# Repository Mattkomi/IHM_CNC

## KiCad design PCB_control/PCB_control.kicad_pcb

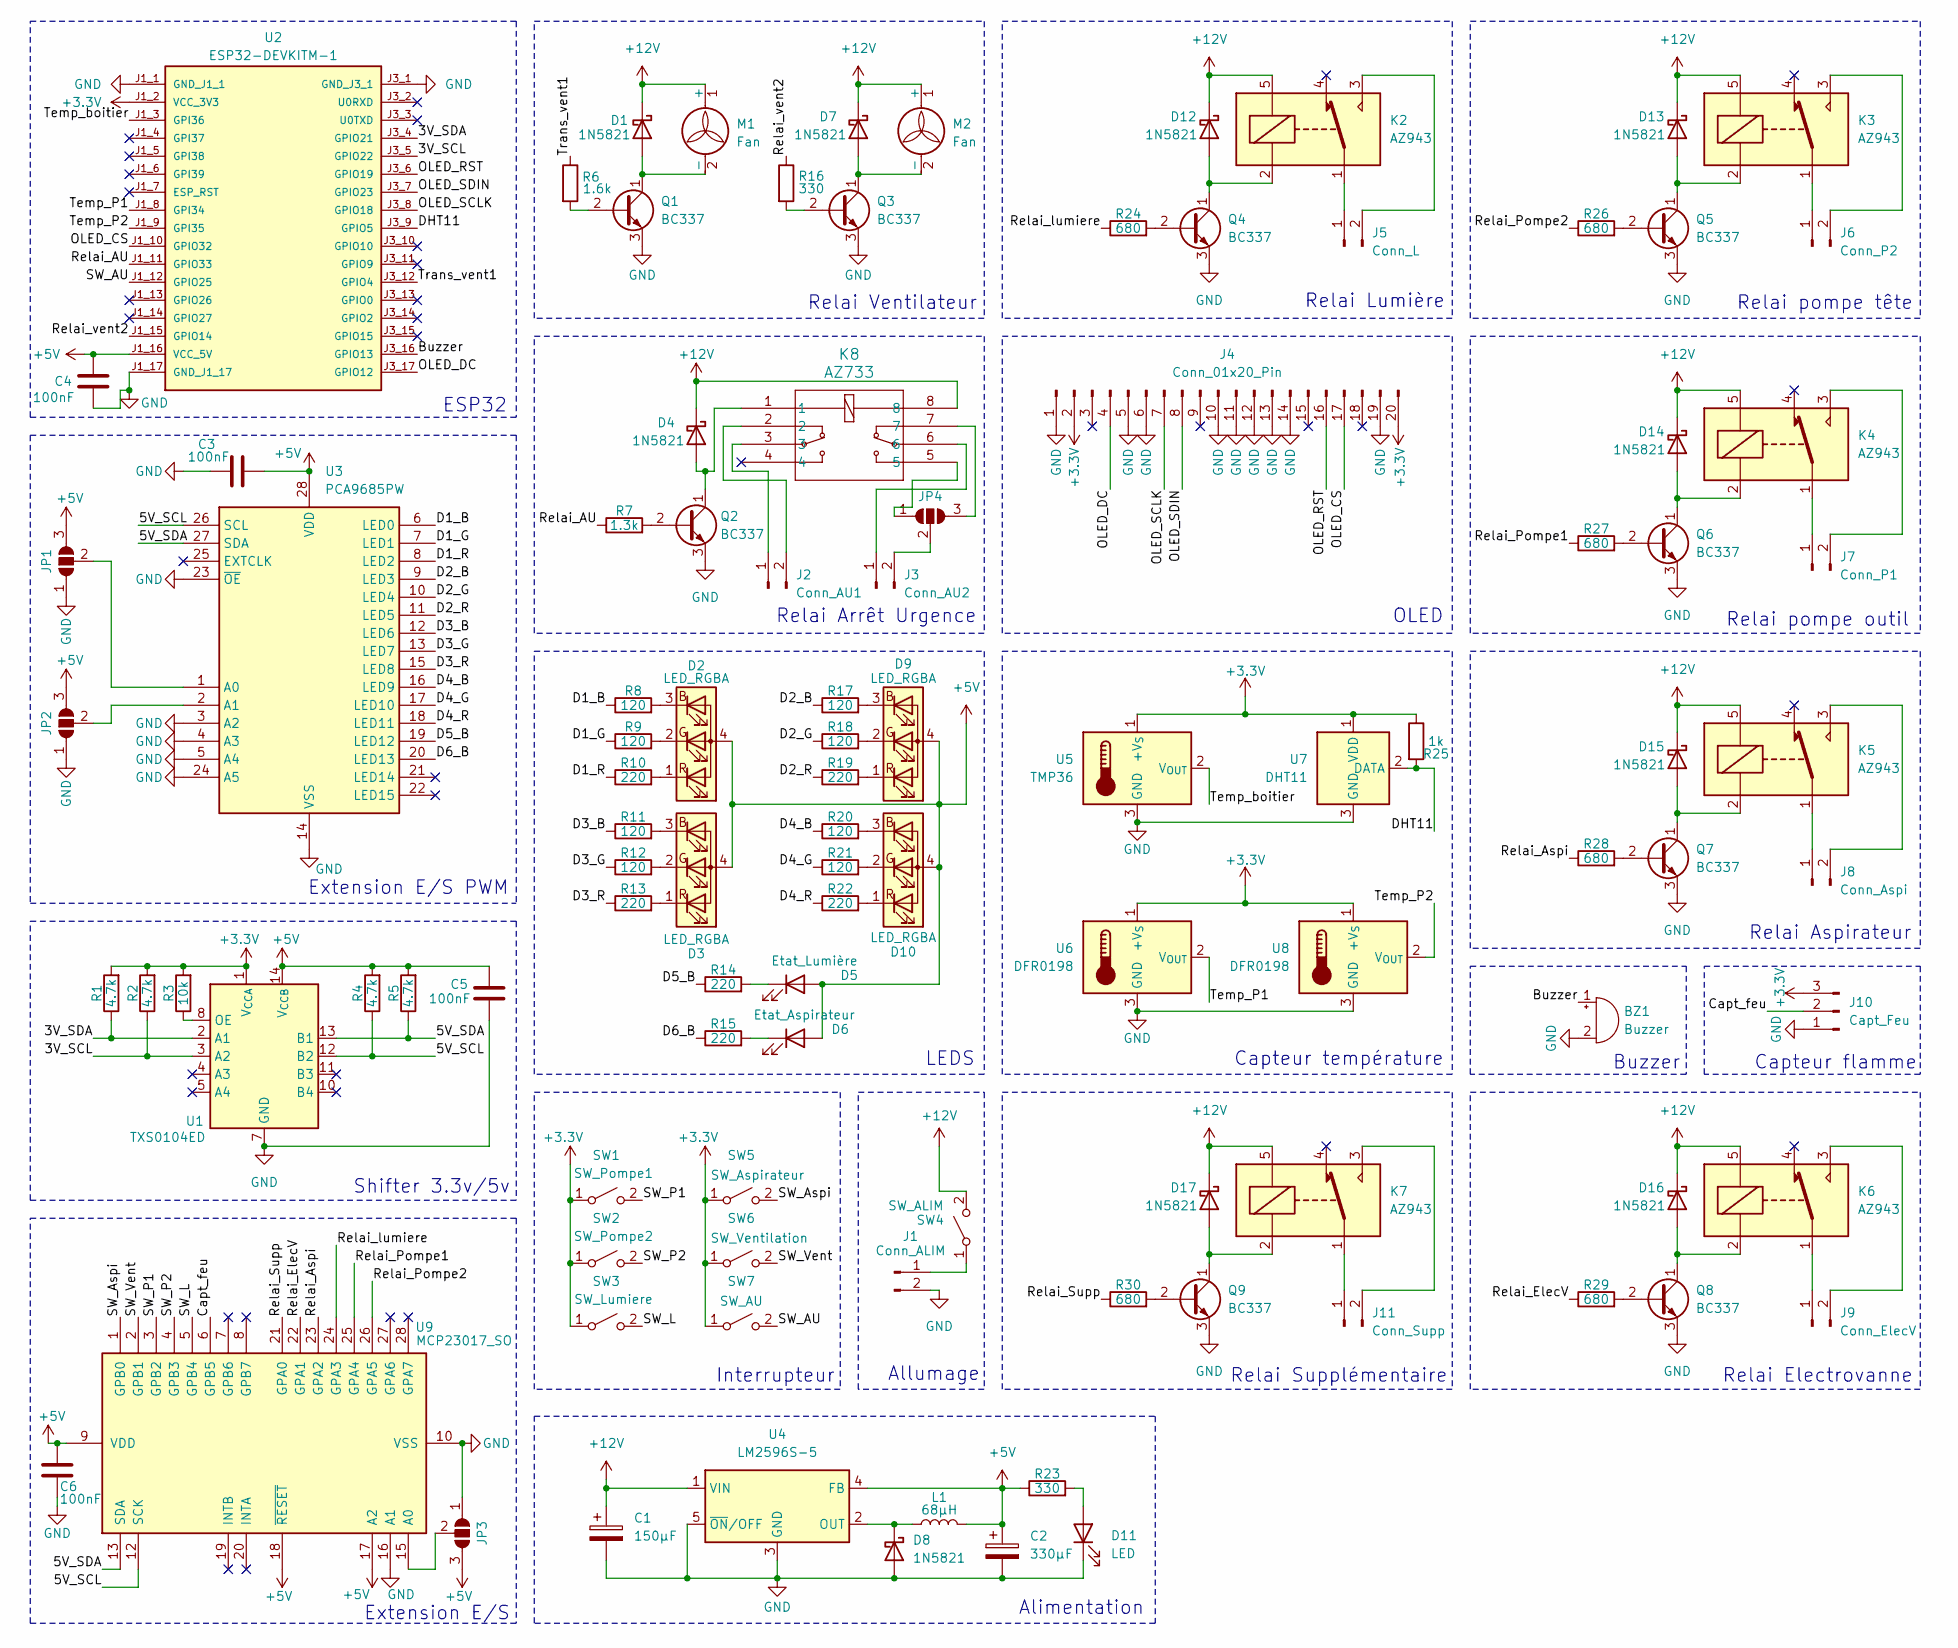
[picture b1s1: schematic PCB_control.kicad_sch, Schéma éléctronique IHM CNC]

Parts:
BZ1: Buzzer; WST-1205S
C1: 150µF; CP_Radial_D6.3mm_P2.50mm
C2: 330µF; CP_Radial_D8.0mm_P3.50mm
C3, C4, C5, C6: 100nF; CAP_R82D-7P4X2P6-5P0_KEM
D1, D4, D7, D8, D12, D13, D14, D15, D16, D17: 1N5821; P2_DO-201
D2, D3, D9, D10: LED_RGBA; JST_XH_B4B-XH-A_1x04_P2.50mm_Vertical
D5: Etat_Lumière; JST_XH_B2B-XH-A_1x02_P2.50mm_Vertical
D6: Etat_Aspirateur; JST_XH_B2B-XH-A_1x02_P2.50mm_Vertical
D11: LED; JST_XH_B2B-XH-A_1x02_P2.50mm_Vertical
J1: Conn_ALIM; JST_XH_B2B-XH-A_1x02_P2.50mm_Vertical
J2: Conn_AU1; Molex_Micro-Fit_3.0_43045-0200_2x01_P3.00mm_Horizontal
J3: Conn_AU2; Molex_Micro-Fit_3.0_43045-0200_2x01_P3.00mm_Horizontal
J4: Conn_01x20_Pin; JST_XH_B20B-XH-A_1x20_P2.50mm_Vertical
J5: Conn_L; Molex_Micro-Fit_3.0_43045-0200_2x01_P3.00mm_Horizontal
J6: Conn_P2; Molex_Micro-Fit_3.0_43045-0200_2x01_P3.00mm_Horizontal
J7: Conn_P1; Molex_Micro-Fit_3.0_43045-0200_2x01_P3.00mm_Horizontal
J8: Conn_Aspi; Molex_Micro-Fit_3.0_43045-0200_2x01_P3.00mm_Horizontal
J9: Conn_ElecV; Molex_Micro-Fit_3.0_43045-0200_2x01_P3.00mm_Horizontal
J10: Capt_Feu; JST_XH_S3B-XH-A_1x03_P2.50mm_Horizontal
J11: Conn_Supp; Molex_Micro-Fit_3.0_43045-0200_2x01_P3.00mm_Horizontal
JP1, JP2, JP3: SolderJumper_3_Open; SolderJumper-3_P1.3mm_Open_RoundedPad1.0x1.5mm
JP4: SolderJumper_3_Open; SolderJumper-3_P1.3mm_Open_RoundedPad1.0x1.5mm_NumberLabels
K2, K3, K4, K5, K6, K7: AZ943; AZ943-1CH_AMZ
K8: AZ733; AZ733-2C_AMZ
L1: 68µH; L_Bourns_SRR1260
M1: Fan; JST_XH_B2B-XH-A_1x02_P2.50mm_Vertical
M2: Fan; JST_XH_S2B-XH-A-1_1x02_P2.50mm_Horizontal
Q1, Q2, Q3, Q4, Q5, Q6, Q7, Q8, Q9: BC337; TO-92_Inline
R1, R2, R4, R5: 4.7k; R_1206_3216Metric_Pad1.30x1.75mm_HandSolder
R3: 10k; R_1206_3216Metric_Pad1.30x1.75mm_HandSolder
R6: 1.6k; R_1206_3216Metric_Pad1.30x1.75mm_HandSolder
R7: 1.3k; R_1206_3216Metric_Pad1.30x1.75mm_HandSolder
R8, R9, R11, R12, R17, R18, R20, R21: 120; R_1206_3216Metric_Pad1.30x1.75mm_HandSolder
R10, R13, R14, R15, R19, R22: 220; R_1206_3216Metric_Pad1.30x1.75mm_HandSolder
R16, R23: 330; R_1206_3216Metric_Pad1.30x1.75mm_HandSolder
R24, R26, R27, R28, R29, R30: 680; R_1206_3216Metric_Pad1.30x1.75mm_HandSolder
R25: 1k; R_1206_3216Metric_Pad1.30x1.75mm_HandSolder
SW1: SW_Pompe1; JST_XH_B2B-XH-A_1x02_P2.50mm_Vertical
SW2: SW_Pompe2; JST_XH_B2B-XH-A_1x02_P2.50mm_Vertical
SW3: SW_Lumiere; JST_XH_B2B-XH-A_1x02_P2.50mm_Vertical
SW4: SW_ALIM; JST_XH_B2B-XH-A_1x02_P2.50mm_Vertical
SW5: SW_Aspirateur; JST_XH_B2B-XH-A_1x02_P2.50mm_Vertical
SW6: SW_Ventilation; JST_XH_B2B-XH-A_1x02_P2.50mm_Vertical
SW7: SW_AU; JST_XH_B2B-XH-A_1x02_P2.50mm_Vertical
U1: TXS0104ED; SOIC-14_3.9x8.7mm_P1.27mm
U2: ESP32-DEVKITM-1; MODULE_ESP32-DEVKITM-1; PARTREV 1.0
U3: PCA9685PW; TSSOP-28_4.4x9.7mm_P0.65mm
U4: LM2596S-5; TO-263-5_TabPin3
U5: TMP36; TO-92_Inline
U6, U8: DFR0198; JST_XH_S3B-XH-A_1x03_P2.50mm_Horizontal
U7: DHT11; JST_XH_S3B-XH-A_1x03_P2.50mm_Horizontal
U9: MCP23017_SO; TSSOP-28_4.4x9.7mm_P0.65mm

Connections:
+3.3V: J4.2, J4.20, J10.3, R1.2, R2.2, R3.2, R25.1, SW1.1 (A), SW2.1 (A), SW3.1 (A), SW5.1 (A), SW6.1 (A), SW7.1 (A), U1.1 (V_{CCA}), U2.J1_2 (VCC_3V3), U5.1 (+V_{S}), U6.1 (+V_{S}), U7.1 (VDD), U8.1 (+V_{S})
+5V: C2.1, C3.2, C4.1, C5.1, C6.1, D2.4 (A), D3.4 (A), D5.2 (A), D6.2 (A), D9.4 (A), D10.4 (A), JP1.3 (B), JP2.3 (B), JP3.3 (B), L1.2, R4.2, R5.2, R23.1, U1.14 (V_{CCB}), U2.J1_16 (VCC_5V), U3.28 (VDD), U4.4 (FB), U9.9 (VDD), U9.17 (A2), U9.18 (~RESET)
+12V: C1.1, D1.1 (K), D4.1 (K), D7.1 (K), D12.1 (K), D13.1 (K), D14.1 (K), D15.1 (K), D16.1 (K), D17.1 (K), K2.5, K3.5, K4.5, K5.5, K6.5, K7.5, K8.8, M1.1 (+), M2.1 (+), SW4.2 (B), U4.1 (VIN)
/3V_SCL: R2.1, U1.3 (A2), U2.J3_5 (GPIO22)
/3V_SDA: R1.1, U1.2 (A1), U2.J3_4 (GPIO21)
/5V_SCL: R4.1, U1.12 (B2), U3.26 (SCL), U9.12 (SCK)
/5V_SDA: R5.1, U1.13 (B1), U3.27 (SDA), U9.13 (SDA)
/Buzzer: BZ1.1 (+), U2.J3_16 (GPIO13)
/Capt_feu: J10.2, U9.6 (GPB5)
/D1_B: R8.1, U3.6 (LED0)
/D1_G: R9.1, U3.7 (LED1)
/D1_R: R10.1, U3.8 (LED2)
/D2_B: R17.1, U3.9 (LED3)
/D2_G: R18.1, U3.10 (LED4)
/D2_R: R19.1, U3.11 (LED5)
/D3_B: R11.1, U3.12 (LED6)
/D3_G: R12.1, U3.13 (LED7)
/D3_R: R13.1, U3.15 (LED8)
/D4_B: R20.1, U3.16 (LED9)
/D4_G: R21.1, U3.17 (LED10)
/D4_R: R22.1, U3.18 (LED11)
/D5_B: R14.1, U3.19 (LED12)
/D6_B: R15.1, U3.20 (LED13)
/DHT11: R25.2, U2.J3_9 (GPIO5), U7.2 (DATA)
/OLED_CS: J4.17, U2.J1_10 (GPIO32)
/OLED_DC: J4.4, U2.J3_17 (GPIO12)
/OLED_RST: J4.16, U2.J3_6 (GPIO19)
/OLED_SCLK: J4.7, U2.J3_8 (GPIO18)
/OLED_SDIN: J4.8, U2.J3_7 (GPIO23)
/Relai_AU: R7.1, U2.J1_11 (GPIO33)
/Relai_Aspi: R28.1, U9.23 (GPA2)
/Relai_ElecV: R29.1, U9.22 (GPA1)
/Relai_Pompe1: R27.1, U9.25 (GPA4)
/Relai_Pompe2: R26.1, U9.26 (GPA5)
/Relai_Supp: R30.1, U9.21 (GPA0)
/Relai_lumiere: R24.1, U9.24 (GPA3)
/Relai_vent2: R16.1, U2.J1_15 (GPIO14)
/SW_AU: SW7.2 (B), U2.J1_12 (GPIO25)
/SW_Aspi: SW5.2 (B), U9.1 (GPB0)
/SW_L: SW3.2 (B), U9.5 (GPB4)
/SW_P1: SW1.2 (B), U9.3 (GPB2)
/SW_P2: SW2.2 (B), U9.4 (GPB3)
/SW_Vent: SW6.2 (B), U9.2 (GPB1)
/Temp_P1: U2.J1_8 (GPI34), U6.2 (V_{OUT})
/Temp_P2: U2.J1_9 (GPI35), U8.2 (V_{OUT})
/Temp_boitier: U2.J1_3 (GPI36), U5.2 (V_{OUT})
/Trans_vent1: R6.1, U2.J3_12 (GPIO4)
GND: BZ1.2 (-), C1.2, C2.2, C3.1, C4.2, C5.2, C6.2, D8.2 (A), D11.1 (K), J1.2, J4.1, J4.5, J4.6, J4.10, J4.11, J4.12, J4.13, J4.14, J4.19, J10.1, JP1.1 (A), JP2.1 (A), JP3.1 (A), Q1.3 (E), Q2.3 (E), Q3.3 (E), Q4.3 (E), Q5.3 (E), Q6.3 (E), Q7.3 (E), Q8.3 (E), Q9.3 (E), U1.7 (GND), U2.J1_1 (GND_J1_1), U2.J1_17 (GND_J1_17), U2.J3_1 (GND_J3_1), U3.3 (A2), U3.4 (A3), U3.5 (A4), U3.14 (VSS), U3.23 (~OE), U3.24 (A5), U4.3 (GND), U4.5 (~ON/OFF), U5.3 (GND), U6.3 (GND), U7.3 (GND), U8.3 (GND), U9.10 (VSS), U9.16 (A1)
unnamed: D1.2 (A), M1.2 (-), Q1.1 (C)
unnamed: D2.3 (BK), R8.2
unnamed: D2.2 (GK), R9.2
unnamed: D2.1 (RK), R10.2
unnamed: D3.3 (BK), R11.2
unnamed: D3.2 (GK), R12.2
unnamed: D3.1 (RK), R13.2
unnamed: D4.2 (A), K8.1, Q2.1 (C)
unnamed: D5.1 (K), R14.2
unnamed: D6.1 (K), R15.2
unnamed: D7.2 (A), M2.2 (-), Q3.1 (C)
unnamed: D8.1 (K), L1.1, U4.2 (OUT)
unnamed: D9.3 (BK), R17.2
unnamed: D9.2 (GK), R18.2
unnamed: D9.1 (RK), R19.2
unnamed: D10.3 (BK), R20.2
unnamed: D10.2 (GK), R21.2
unnamed: D10.1 (RK), R22.2
unnamed: D11.2 (A), R23.2
unnamed: D12.2 (A), K2.2, Q4.1 (C)
unnamed: D13.2 (A), K3.2, Q5.1 (C)
unnamed: D14.2 (A), K4.2, Q6.1 (C)
unnamed: D15.2 (A), K5.2, Q7.1 (C)
unnamed: D16.2 (A), K6.2, Q8.1 (C)
unnamed: D17.2 (A), K7.2, Q9.1 (C)
unnamed: J1.1, SW4.1 (A)
unnamed: J2.1, K8.3
unnamed: J2.2, K8.2
unnamed: J3.1, K8.6
unnamed: J3.2, JP4.2 (C)
unnamed: J5.1, K2.1
unnamed: J5.2, K2.3
unnamed: J6.1, K3.1
unnamed: J6.2, K3.3
unnamed: J7.1, K4.1
unnamed: J7.2, K4.3
unnamed: J8.1, K5.1
unnamed: J8.2, K5.3
unnamed: J9.1, K6.1
unnamed: J9.2, K6.3
unnamed: J11.1, K7.1
unnamed: J11.2, K7.3
unnamed: JP1.2 (C), U3.1 (A0)
unnamed: JP2.2 (C), U3.2 (A1)
unnamed: JP3.2 (C), U9.15 (A0)
unnamed: JP4.1 (A), K8.5
unnamed: JP4.3 (B), K8.7
unnamed: Q1.2 (B), R6.2
unnamed: Q2.2 (B), R7.2
unnamed: Q3.2 (B), R16.2
unnamed: Q4.2 (B), R24.2
unnamed: Q5.2 (B), R26.2
unnamed: Q6.2 (B), R27.2
unnamed: Q7.2 (B), R28.2
unnamed: Q8.2 (B), R29.2
unnamed: Q9.2 (B), R30.2
unnamed: R3.1, U1.8 (OE)

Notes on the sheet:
Relai Lumière
Capteur température
Relai Supplémentaire
Shifter 3.3v/5v
Alimentation
Buzzer
ESP32
Capteur flamme
LEDS
Relai Ventilateur
Relai Electrovanne
Relai Arrêt Urgence
Extension E/S PWM
Relai pompe tête
Relai Aspirateur
Extension E/S
Allumage
Relai pompe outil
Interrupteur
OLED

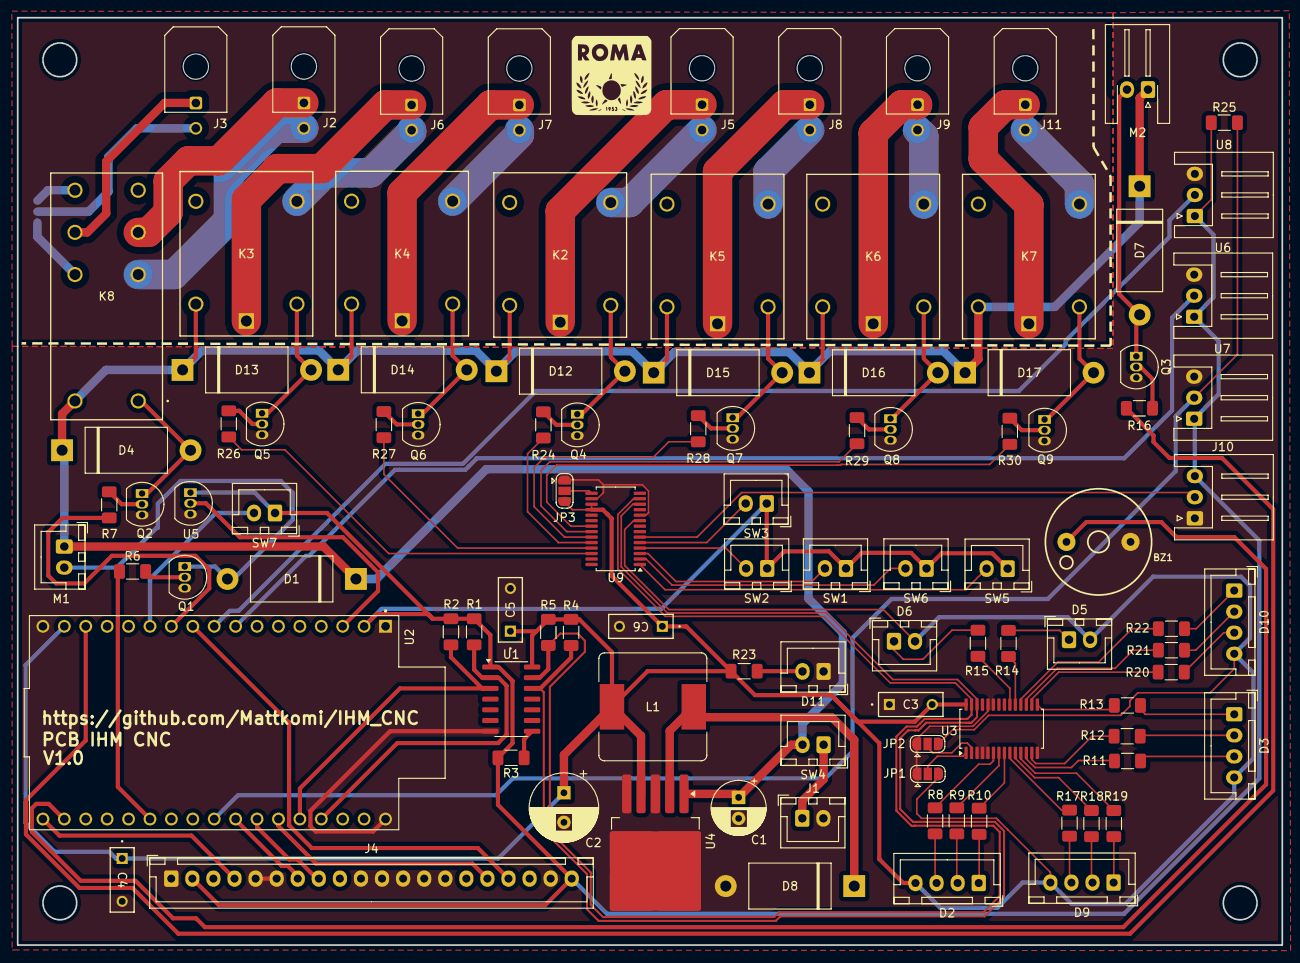
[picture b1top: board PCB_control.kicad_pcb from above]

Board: 2 copper layers, 150.0 x 110.0 mm, 104 parts (1 on the bottom side), 105 nets.

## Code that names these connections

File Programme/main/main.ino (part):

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
//Attribution des pins de l'ESP
            //----- Input -----
#define SW_AU  25         //Switch Arrêt d'urgence
#define Cap_DHT11  5          //Data température + humidité
#define Temp_P1  34       //Capteur de température Analogique
#define Temp_P2  35       //Capteur de température Analogique
#define Temp_boitier  36  //Capteur de température Analogique
#define SW_Aspi  0        //Switch de l'aspirateur GPIO déporté MCP
#define SW_Vent  1        //Switch du ventilateur GPIO déporté MCP
#define SW_P1  2          //Switch de la pompe 1 GPIO déporté MCP
#define SW_P2  3          //Switch de la pompe 2 GPIO déporté MCP
#define SW_L  4           //Switch de la lumière GPIO déporté MCP
#define Capt_feu  5       //Capteur de flamme numérique GPIO déporté MCP
            //----- Output -----
#define Relai_AU  33      //Relai qui sectionne l'arrivée de courant de la CNC
#define Trans_vent1  4    //transistor ventilation boitier IHM
#define Buzzer  13        //indicateur sonore
#define Relai_vent2  14   //Ventilation CNC
#define D1_B  0           //LED RGB GPIO déporté PCA
#define D1_G  1           //LED RGB GPIO déporté PCA
#define D1_R  2           //LED RGB GPIO déporté PCA
#define D2_B  3           //LED RGB GPIO déporté PCA
#define D2_G  4           //LED RGB GPIO déporté PCA
#define D2_R  5           //LED RGB GPIO déporté PCA
#define D3_B  6           //LED RGB GPIO déporté PCA
#define D3_G  7           //LED RGB GPIO déporté PCA
#define D3_R  8           //LED RGB GPIO déporté PCA
#define D4_B  9           //LED RGB GPIO déporté PCA
#define D4_G  10          //LED RGB GPIO déporté PCA
#define D4_R  11          //LED RGB GPIO déporté PCA
#define D5_B  12          //LED GPIO déporté PCA
#define D6_B  13          //LED GPIO déporté PCA
#define Relai_Supp  8     //Relai supplémentaire GPIO déporté MCP
#define Relai_ElecV  9    //Relai électrovanne pour arrivé d'air GPIO déporté MCP
#define Relai_Aspi  10    //Relai de l'aspirateur GPIO déporté MCP
#define Relai_lumiere  11 //Relai de la lumière GPIO déporté MCP
#define Relai_Pompe1  12  //Relai de la lumière GPIO déporté MCP
#define Relai_Pompe2  13  //Relai de la lumière GPIO déporté MCP
            //----- OLED ----- 
#define OLED_CS  32       //broche CS de l'OLED
#define OLED_RST  19      //broche Reset de l'OLED
#define OLED_SDIN  23     //broche SDIN de l'OLED
#define OLED_SCLK  18     //broche SCLK de l'OLED
#define OLED_DC  12       //broche DC de l'OLED
U8G2_SSD1322_NHD_128X64_F_3W_SW_SPI u8g2(U8G2_R0,18,23,10,19);//clk,data,cs,reset
            //----- I2C -----
Adafruit_MCP23X17 MCP;
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};

void Setup_pin(){
  pinMode(Temp_boitier, INPUT);
  pinMode(Temp_P1, INPUT);
  pinMode(Temp_P2, INPUT);
  pinMode(SW_AU, INPUT);
  pinMode(Cap_DHT11, INPUT);
  pinMode(Buzzer, OUTPUT);
  pinMode(Relai_AU, OUTPUT);
  pinMode(Trans_vent1, OUTPUT);
  pinMode(Relai_vent2, OUTPUT);
}
void OLED_setup(){
  digitalWrite(OLED_DC,LOW);
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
